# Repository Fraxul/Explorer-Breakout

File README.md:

# Lenovo Explorer cable breakout

This board is designed to replace the captive cable on a Lenovo Explorer Windows Mixed Reality HMD.
It was designed for use in an embedded system where the standard 3m cable is too long, but might be useful for other applications. It should also serve as a reference for the pinout of the explorer's data connector (or at least enough of it to get USB3 and HDMI working).

The project has been successfully tested with boards manufactured by Oshpark.

Note: If you have a 3d printer, print the included spacer and install it between the interface board and the motherboard so you don't put strain on the board-to-board connector. 0.2mm layers, 100% infill, no supports. Lay it flat with the pocket facing up.

### Known Issues

- The USB3 Type-A connector really should be a Type-C connector (or at least not an upstream-facing A connector!)
- The HDMI connector is too close to the USB3 connector: HDMI cables with large strain relief overmolds will not fit side-by-side with a USB3 plug. I use a slimline HDMI cable for this applcation -- MMonoprice 113578 is known to work.

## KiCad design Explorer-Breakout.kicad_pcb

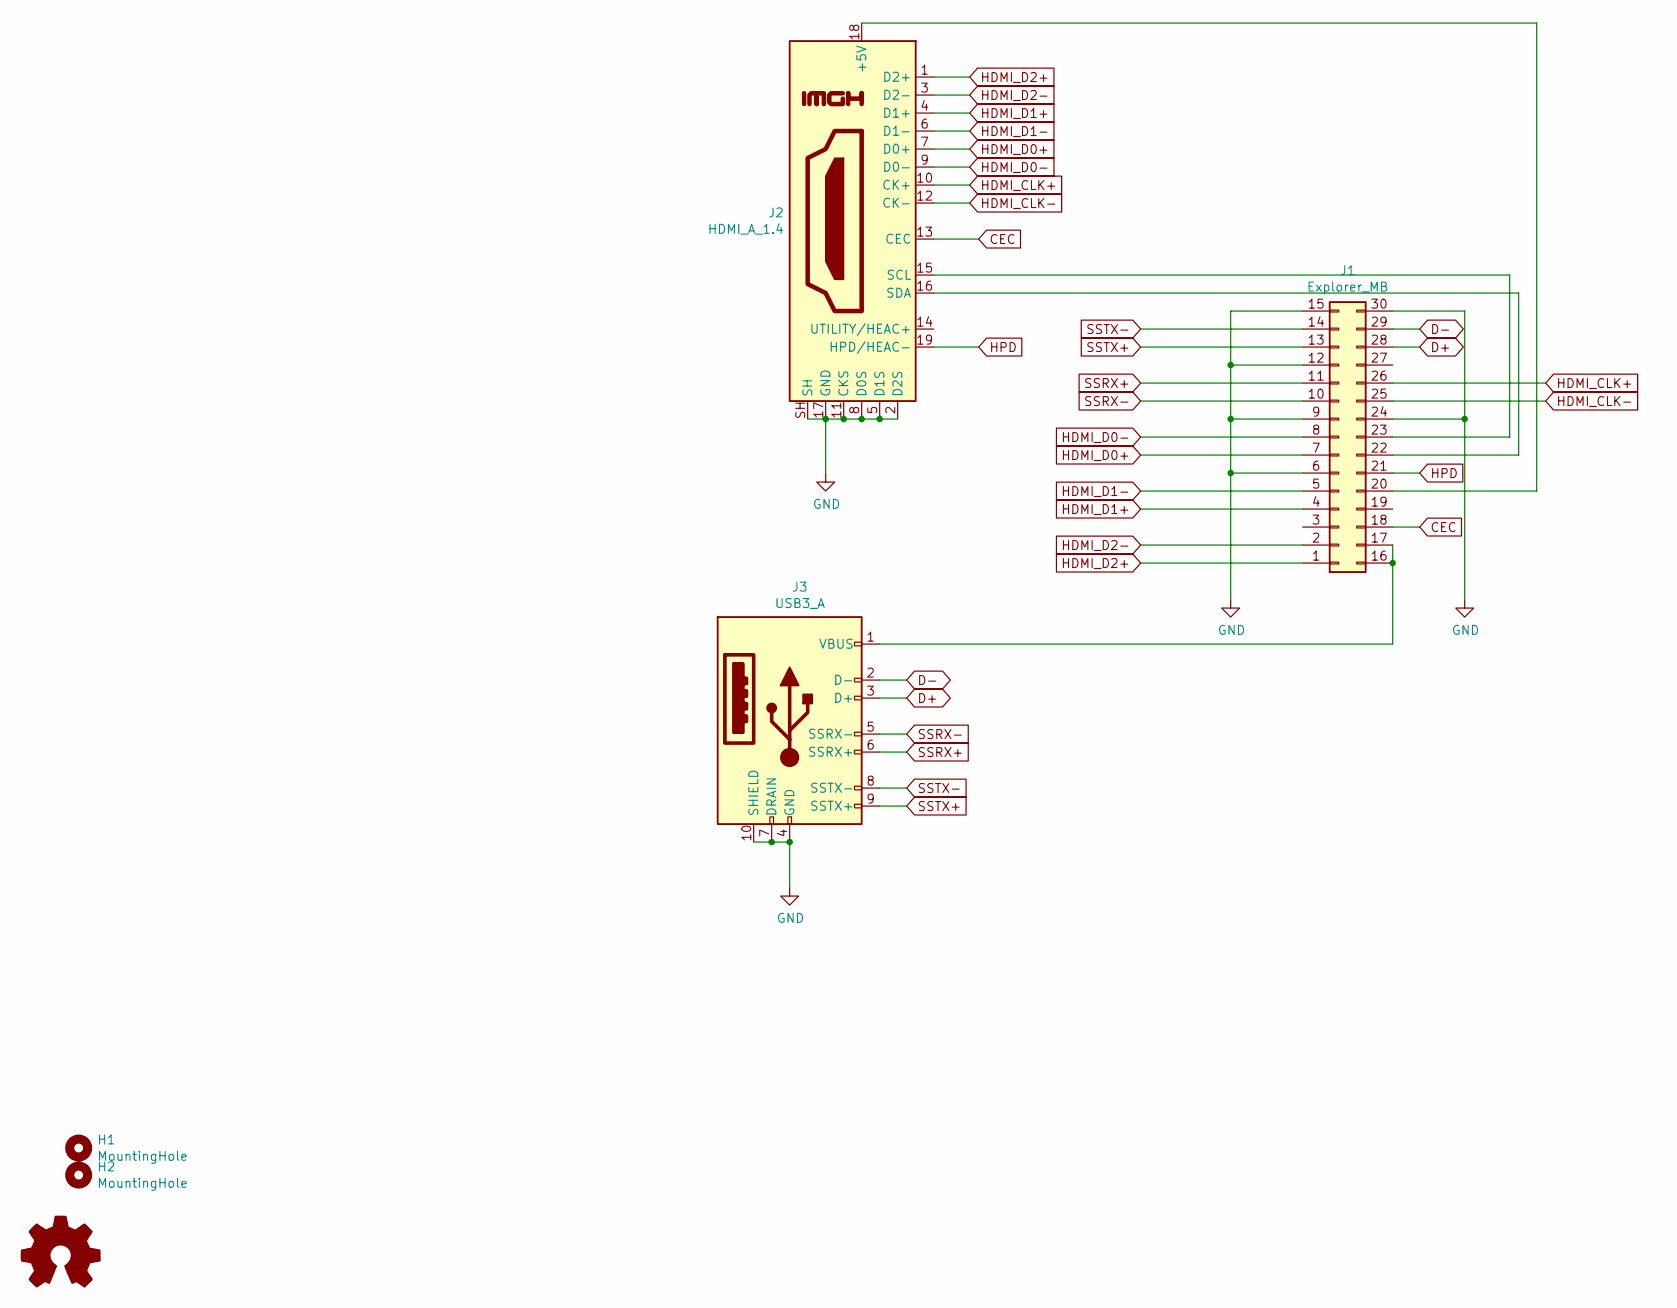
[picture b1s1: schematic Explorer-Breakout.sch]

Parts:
G1: Logo_Open_Hardware_Small; ZoidFace
H1, H2: MountingHole; MountingHole_1.5mm
J1: Explorer_MB; Molex_SlimStack_55560-0307_2x15_P0.50mm_Vertical_ColumnNumb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
J2: HDMI_A_1.4; HDMI_A_Amphenol_10029449-111
J3: USB3_A; USB3_A_Molex_48393-001

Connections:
CEC: J1.18, J2.13 (CEC)
D+: J1.28, J3.3 (D+)
D-: J1.29, J3.2 (D-)
GND: J1.6, J1.9, J1.12, J1.15, J1.24, J1.30, J2.2 (D2S), J2.5 (D1S), J2.8 (D0S), J2.11 (CKS), J2.17 (GND), J2.SH, J3.4 (GND), J3.7 (DRAIN), J3.10 (SHIELD)
HDMI_CLK+: J1.26, J2.10 (CK+)
HDMI_CLK-: J1.25, J2.12 (CK-)
HDMI_D0+: J1.7, J2.7 (D0+)
HDMI_D0-: J1.8, J2.9 (D0-)
HDMI_D1+: J1.4, J2.4 (D1+)
HDMI_D1-: J1.5, J2.6 (D1-)
HDMI_D2+: J1.1, J2.1 (D2+)
HDMI_D2-: J1.2, J2.3 (D2-)
HPD: J1.21, J2.19 (HPD/HEAC-)
unnamed: J1.16, J1.17, J3.1 (VBUS)
unnamed: J1.20, J2.18 (+5V)
unnamed: J1.22, J2.16 (SDA)
unnamed: J1.23, J2.15 (SCL)
SSRX+: J1.11, J3.6 (SSRX+)
SSRX-: J1.10, J3.5 (SSRX-)
SSTX+: J1.13, J3.9 (SSTX+)
SSTX-: J1.14, J3.8 (SSTX-)

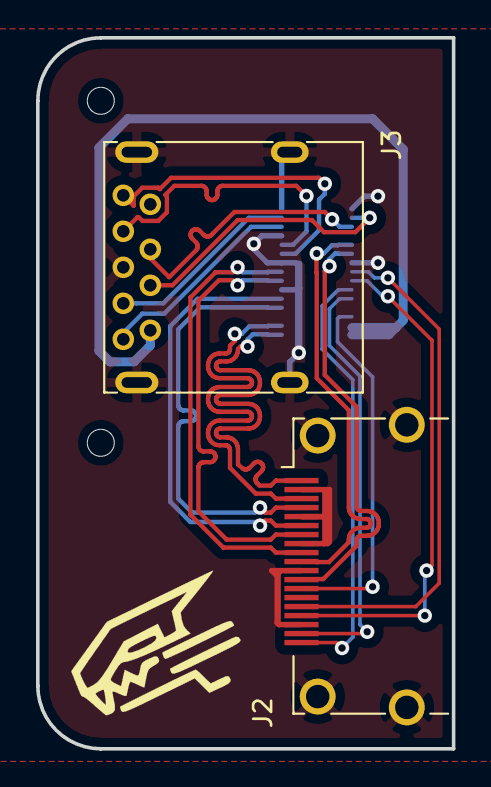
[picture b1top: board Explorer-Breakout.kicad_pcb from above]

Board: 4 copper layers, 23.1 x 39.5 mm, 6 parts (1 on the bottom side), 21 nets.

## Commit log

2022-03-24 Init repo
